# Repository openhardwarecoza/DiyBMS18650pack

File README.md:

# DiyBMSv418650pack
18650 pack with DiyBMSv4

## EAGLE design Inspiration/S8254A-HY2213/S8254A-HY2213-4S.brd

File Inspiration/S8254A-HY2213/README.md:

# S8254A-HY2213-4S
4S Li Battery protector and balance discharger

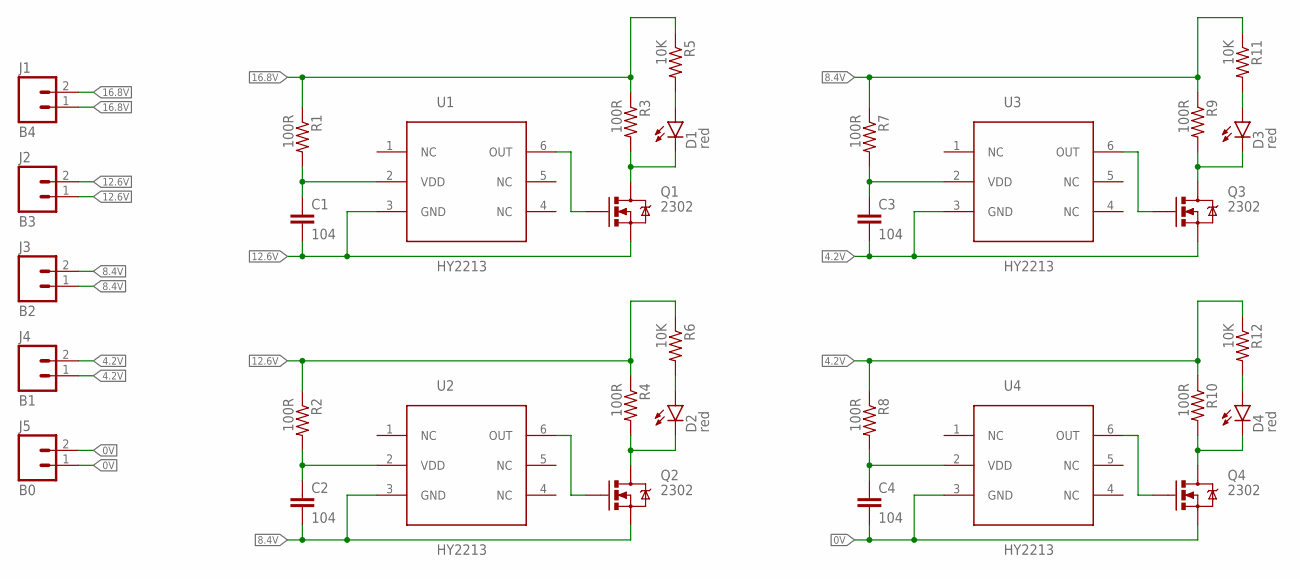
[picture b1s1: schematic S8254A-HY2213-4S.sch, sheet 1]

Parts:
C1, C2, C3, C4: 104; 0603-CAP
D1, D2, D3, D4: red; LED-0603-SEEED
J1: B4; 1X02_NO_SILK
J2: B3; 1X02_NO_SILK
J3: B2; 1X02_NO_SILK
J4: B1; 1X02_NO_SILK
J5: B0; 1X02_NO_SILK
Q1, Q2, Q3, Q4: 2302; SOT23-3
R1, R2, R7, R8: 100R; 0603-RES
R3, R4, R9, R10: 100R; R2512
R5, R6, R11, R12: 10K; 0603-RES
U1, U2, U3, U4: HY2213; SOT23-6

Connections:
0V: C4.2, J5.1, J5.2, Q4.2 (S), U4.3 (GND); also elsewhere on the board
4.2V: C3.2, J4.1, J4.2, Q3.2 (S), R8.1, R10.1, R12.1, U3.3 (GND); also elsewhere on the board
8.4V: C2.2, J3.1, J3.2, Q2.2 (S), R7.1, R9.1, R11.1, U2.3 (GND); also elsewhere on the board
12.6V: C1.2, J2.1, J2.2, Q1.2 (S), R2.1, R4.1, R6.1, U1.3 (GND); also elsewhere on the board
16.8V: J1.1, J1.2, R1.1, R3.1, R5.1; also elsewhere on the board
unnamed: C1.1, R1.2, U1.2 (VDD)
unnamed: Q1.1 (G), U1.6 (OUT)
unnamed: D1.- (C), Q1.3 (D), R3.2
unnamed: C2.1, R2.2, U2.2 (VDD)
unnamed: Q2.1 (G), U2.6 (OUT)
unnamed: D2.- (C), Q2.3 (D), R4.2
unnamed: C3.1, R7.2, U3.2 (VDD)
unnamed: Q3.1 (G), U3.6 (OUT)
unnamed: D3.- (C), Q3.3 (D), R9.2
unnamed: C4.1, R8.2, U4.2 (VDD)
unnamed: Q4.1 (G), U4.6 (OUT)
unnamed: D4.- (C), Q4.3 (D), R10.2
unnamed: D1.+ (A), R5.2
unnamed: D2.+ (A), R6.2
unnamed: D3.+ (A), R11.2
unnamed: D4.+ (A), R12.2

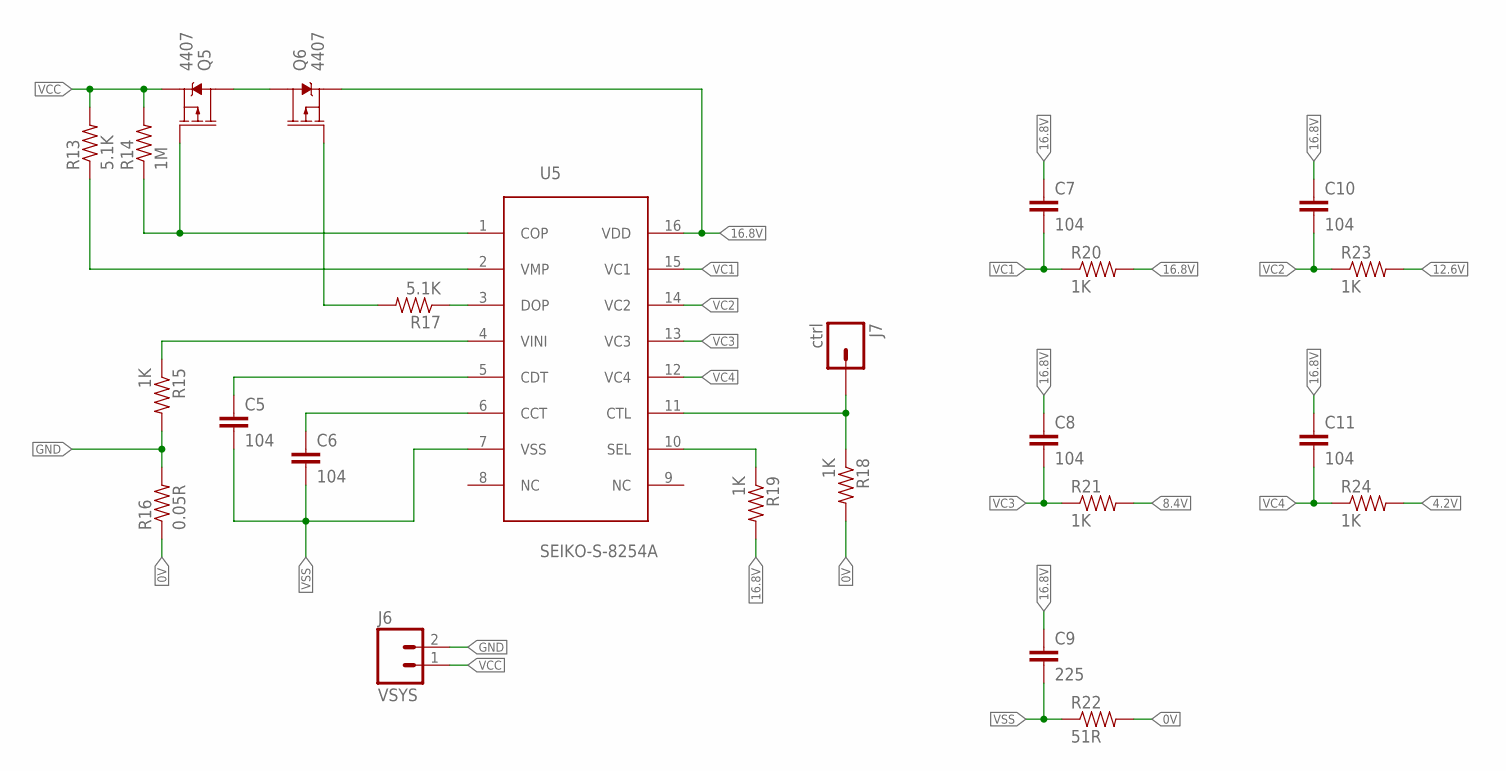
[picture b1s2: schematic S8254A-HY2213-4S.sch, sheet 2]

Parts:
C5, C6, C7, C8, C10, C11: 104; 0603-CAP
C9: 225; 0603-CAP
J6: VSYS; 1X02_NO_SILK
J7: ctrl; 1X01
Q5, Q6: 4407; SO08
R13, R17: 5.1K; 0603-RES
R14: 1M; 0603-RES
R15, R18, R19, R20, R21, R23, R24: 1K; 0603-RES
R16: 0.05R; R2512
R22: 51R; 0603-RES
U5: SEIKO-S-8254A; TSSOP16

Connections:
0V: R16.1, R18.2, R22.2; also elsewhere on the board
4.2V: R24.2; also elsewhere on the board
8.4V: R21.2; also elsewhere on the board
12.6V: R23.2; also elsewhere on the board
16.8V: C7.1, C8.1, C9.1, C10.1, C11.1, Q6.1 (S), Q6.2 (S), Q6.3 (S), R19.2, R20.2, U5.16 (VDD); also elsewhere on the board
GND: J6.2, R15.2, R16.2
unnamed: R19.1, U5.10 (SEL)
unnamed: J7.1, R18.1, U5.11 (CTL)
unnamed: Q5.4 (G), R14.1, U5.1 (COP)
unnamed: R17.1, U5.3 (DOP)
unnamed: Q6.4 (G), R17.2
unnamed: R13.1, U5.2 (VMP)
unnamed: R15.1, U5.4 (VINI)
unnamed: C5.1, U5.5 (CDT)
unnamed: C6.1, U5.6 (CCT)
QQ: Q5.5 (D), Q5.6 (D), Q5.7 (D), Q5.8 (D), Q6.5 (D), Q6.6 (D), Q6.7 (D), Q6.8 (D)
VC1: C7.2, R20.1, U5.15 (VC1)
VC2: C10.2, R23.1, U5.14 (VC2)
VC3: C8.2, R21.1, U5.13 (VC3)
VC4: C11.2, R24.1, U5.12 (VC4)
VCC: J6.1, Q5.1 (S), Q5.2 (S), Q5.3 (S), R13.2, R14.2
VSS: C5.2, C6.2, C9.2, R22.1, U5.7 (VSS)

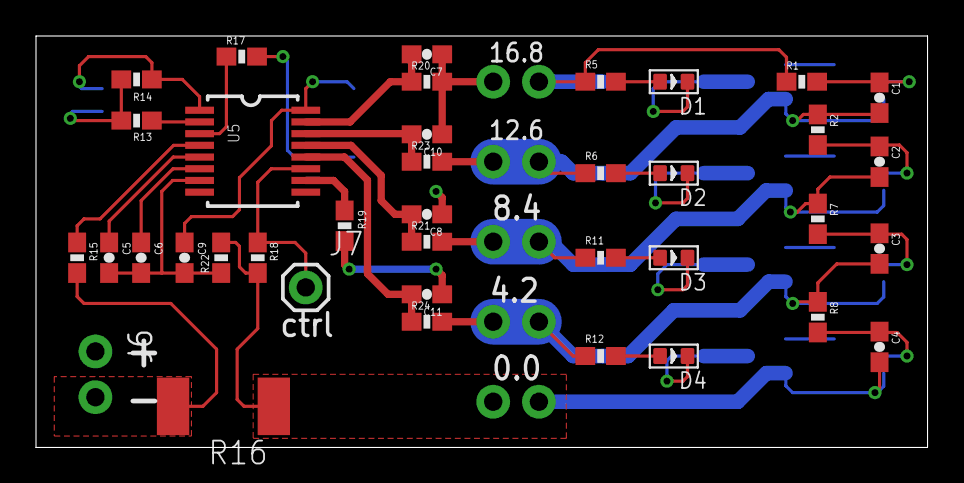
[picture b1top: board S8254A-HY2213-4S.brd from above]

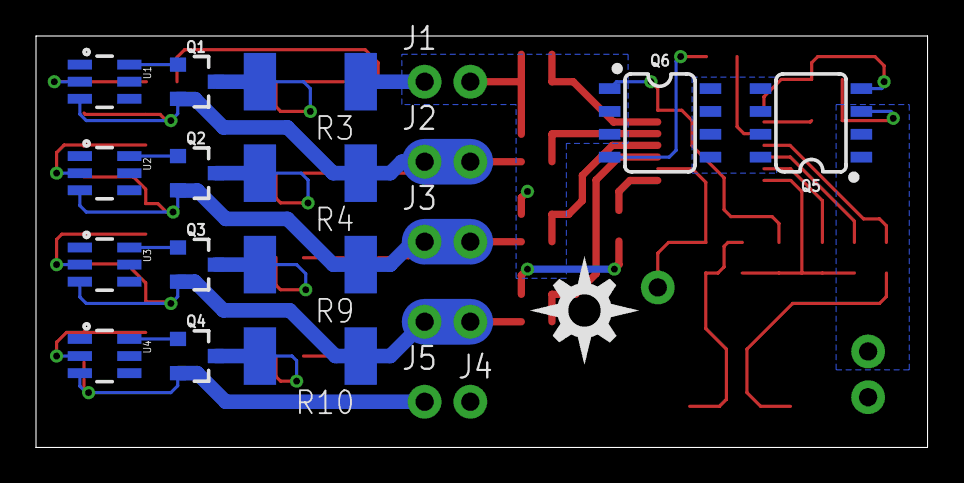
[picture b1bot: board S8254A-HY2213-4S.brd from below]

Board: 2 copper layers, 49.5 x 22.9 mm, 58 parts (20 on the bottom side), 38 nets.

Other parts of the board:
U$1: DIYNOVA_LOGO

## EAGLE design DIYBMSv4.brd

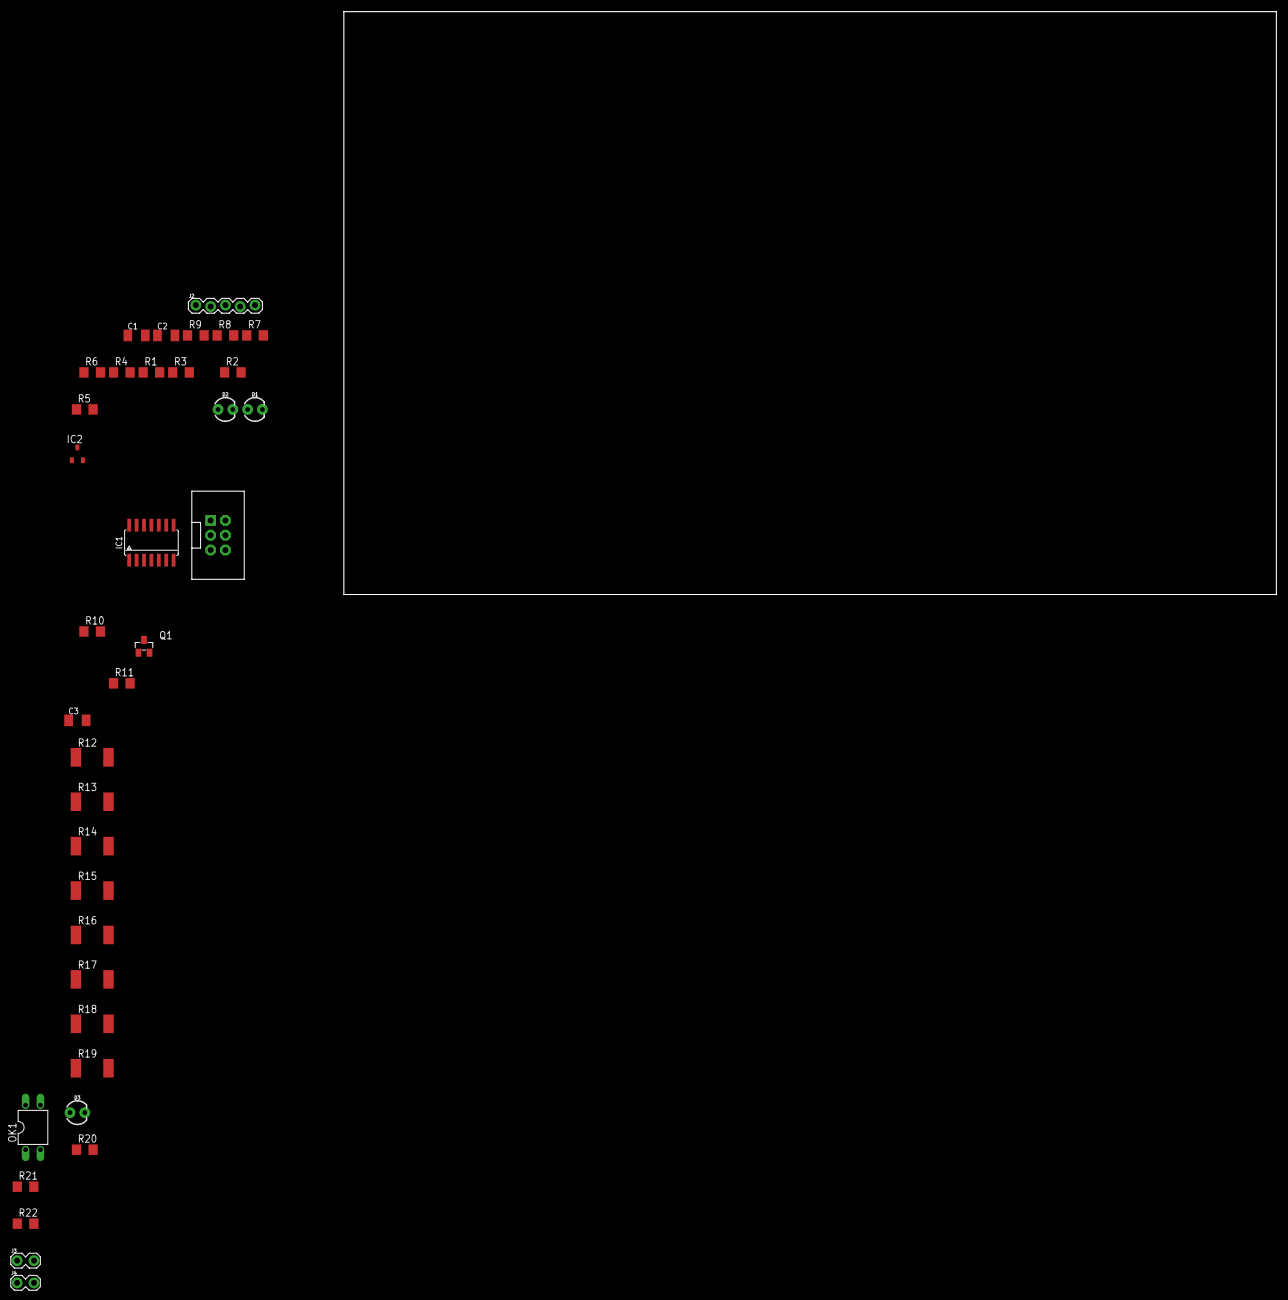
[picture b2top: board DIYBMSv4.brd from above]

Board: 2 copper layers, 160.0 x 100.0 mm, 36 parts (0 on the bottom side), 28 nets, no tracks yet.

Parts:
C1: 104; C1206K
C2: 2.2uF; C1206K
C3: 10uF; C1206K
D1: blue; LED_3MM
D2: green; LED_3MM
D3: RED; LED_3MM
IC1: ATTINY441/841-SSU; SOIC14N
IC2: LM4040BIM3-2.0/NOPB 2.048v SOT23-3; DBZ_R-PDSO-G3
J1: AVRISP6_SHROUDED; 2X3-SHROUDED
J2: 1X05_LOCK
J3, J4: 1X02_LOCK
OK1: PC817; DIL04
Q1: IRLML6244TRPBF; SOT-23
R1, R4: 10K; R1206
R2: 475K1%; R1206
R3: 402K1%; R1206
R5: SDNT2012X473F4150FTF; R1206
R6, R11: 47k; R1206
R7, R8, R20: 2K2; R1206
R9: 1K; R1206
R10: 510R; R1206
R12, R13, R14, R15, R16, R17, R18, R19: 2R2; R2512
R21, R22: 220R; R1206

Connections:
2_VOLT: C2.1, IC1.13, IC2.1, J2.2, R5.1, R9.2
DUMP_LOAD_ENABLE: IC1.10, R10.1
ENABLE: IC1.6, J2.4, R2.1, R9.1
GND: C1.2, C2.2, C3.2, IC1.14, IC2.2, J1.6, J2.5, OK1.2, Q1.2, R3.2, R4.2, R6.2, R7.1, R8.1, R11.2, R22.1
INPUT1: IC1.5, R2.2, R3.1
MISO/TXD1: D1.A, IC1.8, J1.1
MOSI: D2.A, IC1.7, J1.4
unnamed: C3.1, Q1.1, R10.2, R11.1
unnamed: D2.K, R8.2
unnamed: D1.K, R7.2
unnamed: R13.2, R14.1
unnamed: R12.2, R15.1
unnamed: R15.2, R17.1
unnamed: R14.2, R16.1
unnamed: R16.2, R18.1
unnamed: R17.2, R19.1
unnamed: Q1.3, R12.1, R13.1, R20.1
unnamed: D3.K, R20.2
unnamed: OK1.1, R21.2
PB_0: IC1.2, J2.1, R4.1
PB_1: IC1.3, J2.3
RESET: IC1.4, J1.5, R1.1
RXD0: IC1.11, J4.2, R22.2
SCK/RXD1: IC1.9, J1.3, R5.2, R6.1
TX1LOAD: J3.2, OK1.3
TX1VCC: J3.1, OK1.4
TXD0: IC1.12, R21.1
VCC: C1.1, D3.A, IC1.1, J1.2, J4.1, R1.2, R18.2, R19.2

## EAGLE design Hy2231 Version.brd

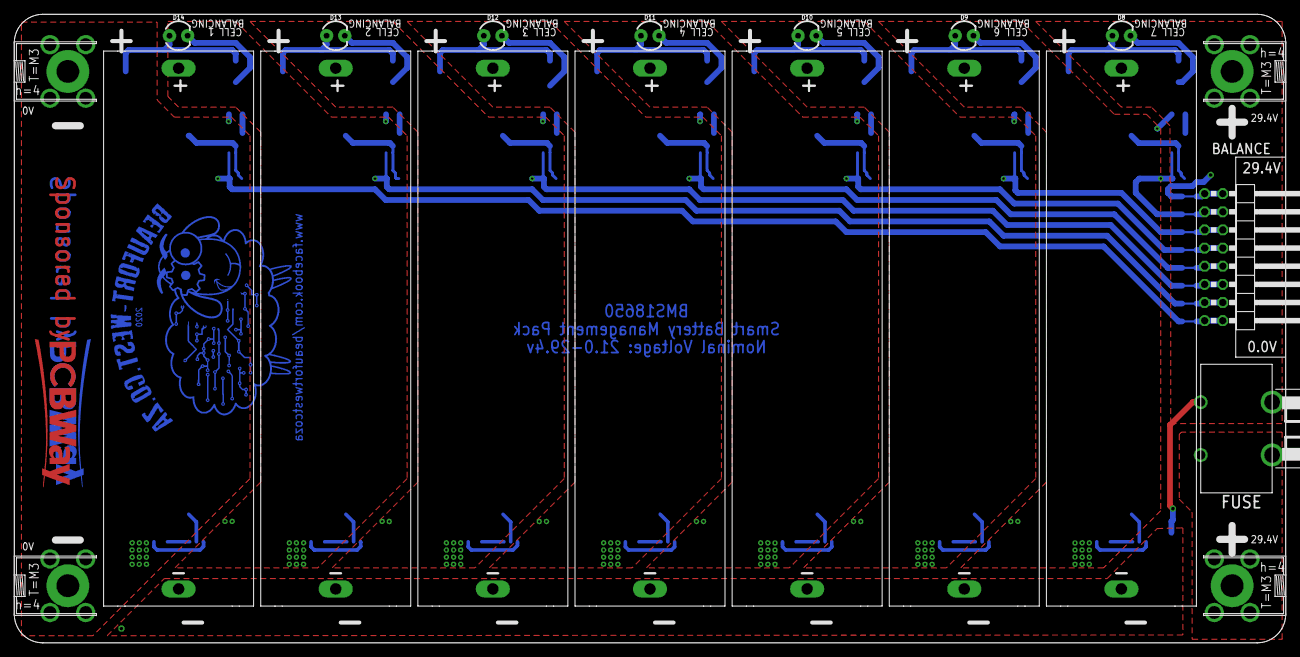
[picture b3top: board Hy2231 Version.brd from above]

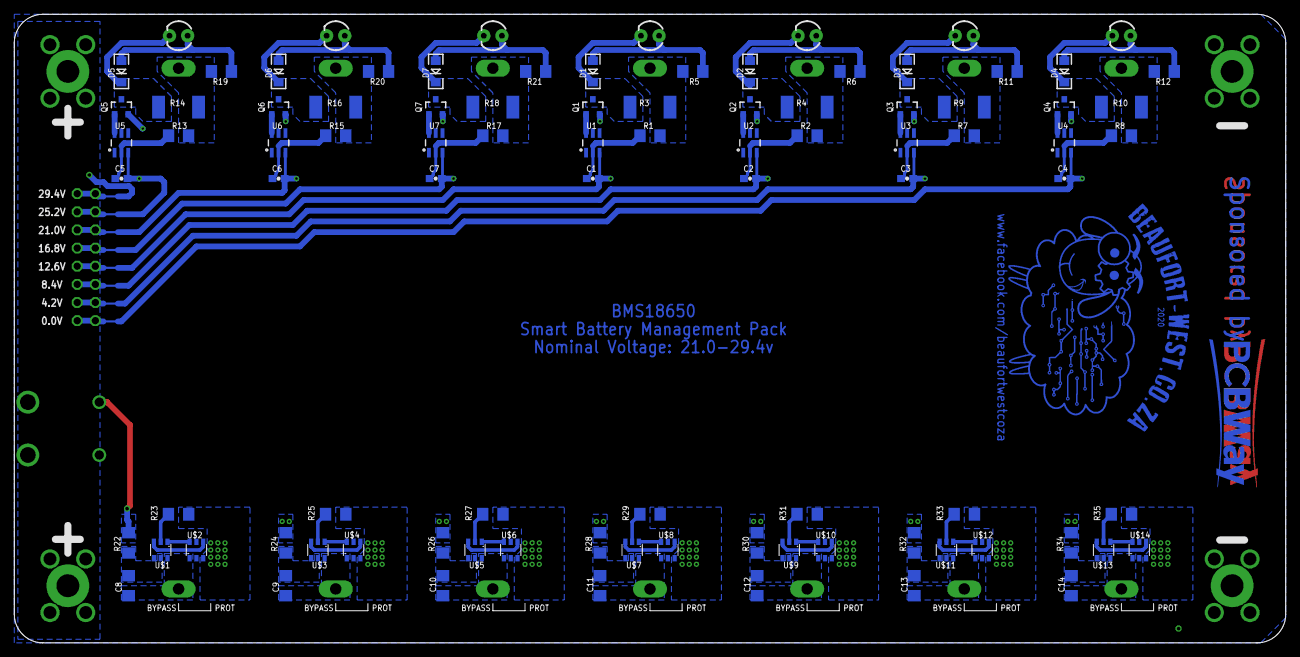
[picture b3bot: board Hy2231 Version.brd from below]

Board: 2 copper layers, 178.0 x 88.0 mm, 104 parts (84 on the bottom side), 72 nets.

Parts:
C1, C2, C3, C4, C5, C6, C7: 104; 0603-CAP
C8, C9, C10, C11, C12, C13, C14: 0.1UF; C1206@1
CON1, CON2, CON7, CON8: PCB-2M3; PCB2-M3
D1, D2, D3, D4, D5, D6, D7: red; LED-1206
D8, D9, D10, D11, D12, D13, D14: LED_3MM
JP2: 2X08/90
Q1, Q2, Q3, Q4, Q5, Q6, Q7: 2302; SOT23-3
R1, R2, R7, R8, R13, R15, R17: 100R; 1206
R3, R4, R9, R10, R14, R16, R18: 100R; R2512
R5, R6, R11, R12, R19, R20, R21: 10K; 1206
R22, R24, R26, R28, R30, R32, R34: 100; R1206
R23, R25, R27, R29, R31, R33, R35: 2K; R1206
U1, U2, U3, U4, U5, U6, U7: HY2213; SOT23-6
U$1, U$3, U$5, U$7, U$9, U$11, U$13: FS312F-G; SOT23-6
U$2, U$4, U$6, U$8, U$10, U$12, U$14: FS8205; SOT23-6
U$15, U$16, U$17, U$18, U$19, U$20, U$21: 18650SINGLE; 18650PTH-SINGLE
U$22: 18MMFUSEHOLDER

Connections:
0V: C4.2, CON1.P$1, CON1.P$2, CON1.P$3, CON1.P$4, CON7.P$1, CON7.P$2, CON7.P$3, CON7.P$4, JP2.15, JP2.16, Q4.2, R35.1, U4.3, U$14.3
4.2V: C3.2, JP2.13, JP2.14, Q3.2, R8.1, R10.1, R12.1, R33.1, R34.2, U3.3, U$12.3, U$21.POS
8.4V: C2.2, JP2.11, JP2.12, Q2.2, R7.1, R9.1, R11.1, R31.1, R32.2, U2.3, U$10.3, U$20.POS
12.6V: C1.2, JP2.9, JP2.10, Q1.2, R2.1, R4.1, R6.1, R29.1, R30.2, U1.3, U$8.3, U$19.POS
16.8V: C7.2, JP2.7, JP2.8, Q7.2, R1.1, R3.1, R5.1, R27.1, R28.2, U7.3, U$6.3, U$18.POS
21.0V: C6.2, JP2.5, JP2.6, Q6.2, R17.1, R18.1, R21.1, R25.1, R26.2, U6.3, U$4.3, U$17.POS
25.2V: C5.2, JP2.3, JP2.4, Q5.2, R15.1, R16.1, R20.1, R23.1, R24.2, U5.3, U$2.3, U$16.POS
29.4V: JP2.1, JP2.2, R13.1, R14.1, R19.1, R22.2, U$15.POS, U$22.F2.0, U$22.F2.1
unnamed: C1.1, R1.2, U1.2
unnamed: C5.1, R13.2, U5.2
unnamed: Q1.1, U1.6
unnamed: D1.C, D11.K, Q1.3, R3.2
unnamed: Q5.1, U5.6
unnamed: C2.1, R2.2, U2.2
unnamed: Q2.1, U2.6
unnamed: D2.C, D12.K, Q2.3, R4.2
unnamed: C3.1, R7.2, U3.2
unnamed: Q3.1, U3.6
unnamed: D3.C, D13.K, Q3.3, R9.2
unnamed: C4.1, R8.2, U4.2
unnamed: Q4.1, U4.6
unnamed: D4.C, D14.K, Q4.3, R10.2
unnamed: D5.C, D8.K, Q5.3, R14.2
unnamed: C6.1, R15.2, U6.2
unnamed: Q6.1, U6.6
unnamed: D6.C, D9.K, Q6.3, R16.2
unnamed: C7.1, R17.2, U7.2
unnamed: Q7.1, U7.6
unnamed: D7.C, D10.K, Q7.3, R18.2
unnamed: D5.A, D8.A, R19.2
unnamed: D6.A, D9.A, R20.2
unnamed: D7.A, D10.A, R21.2
unnamed: D1.A, D11.A, R5.2
unnamed: R23.2, U$1.2
unnamed: D2.A, D12.A, R6.2
unnamed: R25.2, U$3.2
unnamed: D3.A, D13.A, R11.2
unnamed: R27.2, U$5.2
unnamed: D4.A, D14.A, R12.2
unnamed: R29.2, U$7.2
unnamed: R31.2, U$9.2
unnamed: R33.2, U$11.2
unnamed: R35.2, U$13.2
unnamed: CON2.P$1, CON2.P$2, CON2.P$3, CON2.P$4, CON8.P$1, CON8.P$2, CON8.P$3, CON8.P$4, U$22.F1.0, U$22.F1.1
NEG1: C14.1, U$13.6, U$14.1, U$21.NEG
NEG2: C13.1, U$11.6, U$12.1, U$20.NEG
NEG3: C12.1, U$9.6, U$10.1, U$19.NEG
NEG4: C11.1, U$7.6, U$8.1, U$18.NEG
NEG5: C10.1, U$5.6, U$6.1, U$17.NEG
NEG6: C9.1, U$3.6, U$4.1, U$16.NEG
NEG7: C8.1, U$1.6, U$2.1, U$15.NEG
OC: U$1.3, U$2.4
OC1: U$3.3, U$4.4
OC2: U$5.3, U$6.4
OC3: U$7.3, U$8.4
OC4: U$9.3, U$10.4
OC5: U$11.3, U$12.4
OC6: U$13.3, U$14.4
OD: U$1.1, U$2.6
OD1: U$3.1, U$4.6
OD2: U$5.1, U$6.6
OD3: U$7.1, U$8.6
OD4: U$9.1, U$10.6
OD5: U$11.1, U$12.6
OD6: U$13.1, U$14.6
VCC-PROT: C8.2, R22.1, U$1.5
VCC-PROT1: C9.2, R24.1, U$3.5
VCC-PROT2: C10.2, R26.1, U$5.5
VCC-PROT3: C11.2, R28.1, U$7.5
VCC-PROT4: C12.2, R30.1, U$9.5
VCC-PROT5: C13.2, R32.1, U$11.5
VCC-PROT6: C14.2, R34.1, U$13.5

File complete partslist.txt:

1.  C1, C2, C3, C4, C5, C6, C7       		0.1uF 0603

2.  C8, C9, C10, C11, C12, C13, C14  		0.1uF 1206


3.  CON1, CON2, CON7, CON8			PCB2-M3 Terminal

4.  D1, D2, D3, D4, D5, D6, D7			LED Red 1206

5.  Q1, Q2, Q3, Q4, Q5, Q6, Q7			SI2302cds Mosfet SOT23-3

6.  R3, R4, R9, R10, R14, R16, R18   		100R Resistor 2512
	
7.  R1, R2, R7, R8, R13, R15, R17		100R Resistor 1206
    R22, R24, R26, R28, R30, R32, R34		100R Resistor 1206

8.  R5, R6, R11, R12, R19, R20, R21		10K Resistor 1206

9.  R23, R25, R27, R29, R31, R33, R35		2K Resistor 1206

10. U$1, U$3, U$5, U$7, U$9, U$11, U$13		FS312F-G SOT23-6

11. U$2, U$4, U$6, U$8, U$10, U$12, U$14	FS8205 SOT23-6

12. U$15, U$16, U$17, U$18, U$19, U$20, U$21, U$22	18650 Cell Holder PTH

U1, U2, U3, U4, U5, U6, U7			HY2213 SOT23-6

J1  						2x8 Shrouded IDC header 90 degree

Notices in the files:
parts and their libraries:
SparkFun-LED: Licensing: Creative Commons ShareAlike 4.0 International - https://creativecommons.org/licenses/by-sa/4.0
